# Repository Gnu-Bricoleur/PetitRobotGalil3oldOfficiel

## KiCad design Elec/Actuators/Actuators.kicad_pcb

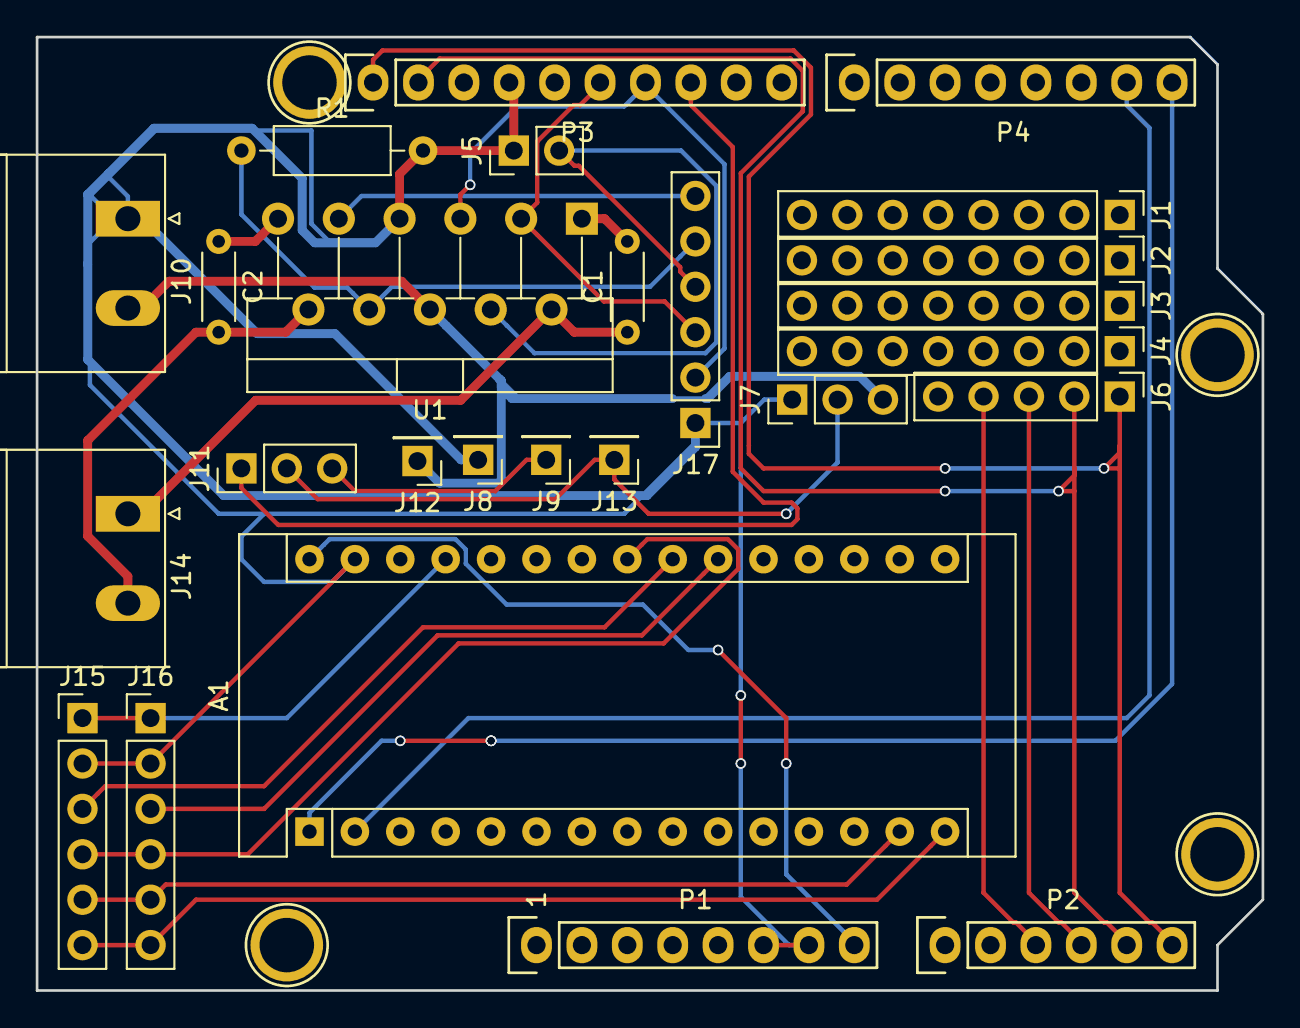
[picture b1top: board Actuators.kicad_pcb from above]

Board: 2 copper layers, 68.6 x 53.3 mm, 30 parts (0 on the bottom side), 27 nets.

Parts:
A1: Arduino_Nano_v3.x; Arduino_Nano
C1, C2: 10nF; R_Axial_DIN0204_L3.6mm_D1.6mm_P5.08mm_Horizontal
J1, J2, J3, J4: Conn_01x08; PinHeader_1x08_P2.54mm_Vertical
J5: Conn_01x02; PinHeader_1x02_P2.54mm_Vertical
J6: Conn_01x05; PinHeader_1x05_P2.54mm_Vertical
J7, J11: Conn_01x03; PinHeader_1x03_P2.54mm_Vertical
J8, J9, J12, J13: Conn_01x01; PinHeader_1x01_P2.54mm_Vertical
J10, J14: Screw_Terminal_01x02; PhoenixContact_MSTBA_2,5_2-G_1x02_P5.00mm_Horizontal
J15, J16, J17: Conn_01x06; PinHeader_1x06_P2.54mm_Vertical
P1: Power; Socket_Strip_Arduino_1x08
P2: Analog; Socket_Strip_Arduino_1x06
P3: Digital; Socket_Strip_Arduino_1x10
P4: Digital; Socket_Strip_Arduino_1x08
P5, P6, P7, P8: CONN_01X01; Arduino_1pin
R1: 2.7k; R_Axial_DIN0207_L6.3mm_D2.5mm_P10.16mm_Horizontal
U1: LMD18200; TO-220-11_P3.4x5.08mm_StaggerOdd_Lead4.85mm_Vertical

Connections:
/0(Rx): A1.1, P4.8
/1(Tx): A1.2, P4.7
/10(**/SS): J11.1, P3.8
/11(**/MOSI): J17.2, P3.7, U1.5
/12(MISO): J17.3, P3.6, U1.3
/A2: J6.4, P2.3
/A3: J6.3, P2.4
/A4(SDA): J6.2, P2.5, P3.2
/A5(SCL): J6.1, P2.6, P3.1
/BR1: J5.2, J17.4, U1.4
/Bat+: J7.3, J10.2, J12.1, U1.6
/CSEN1: J17.5, R1.1, U1.8
/EncAlim: A1.27, J15.1, J16.1
/MISO: A1.15, J15.6, J16.6
/MOSI: A1.14, J15.5, J16.5
/SCK: A1.23, J15.4, J16.4
/SS1: A1.22, J15.3
/SS2: A1.21, J16.3
/TF1: J17.6, U1.9
/Vin: A1.30, P1.8
GND: A1.29, J5.1, J7.1, J8.1, J10.1, J15.2, J16.2, J17.1, P1.6, P1.7, P3.4, R1.2, U1.7
unnamed: C1.1, J14.1, U1.2
unnamed: C1.2, U1.1
unnamed: C2.1, U1.11
unnamed: C2.2, J14.2, U1.10
unnamed: J7.2, J11.2, J13.1
unnamed: J9.1, J11.3

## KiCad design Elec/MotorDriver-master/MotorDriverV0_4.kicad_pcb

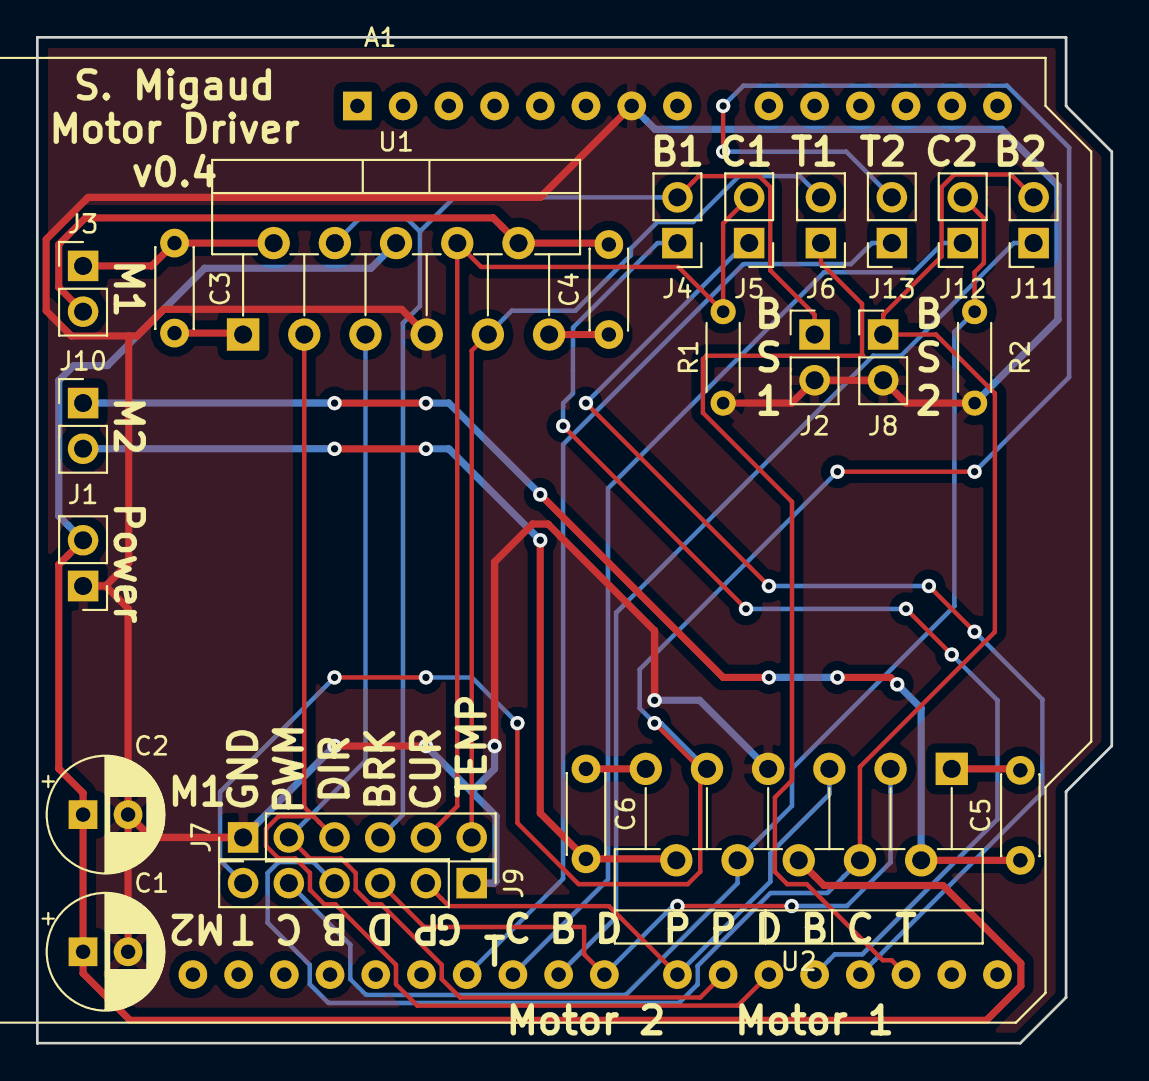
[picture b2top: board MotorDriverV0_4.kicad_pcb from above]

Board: 2 copper layers, 59.7 x 55.9 mm, 24 parts (0 on the bottom side), 26 nets.

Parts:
A1: Arduino_UNO_R3
C1: 1uF; CP_Radial_D6.3mm_P2.50mm
C2: 1200uF; CP_Radial_D6.3mm_P2.50mm
C3, C4, C5, C6: 10nF; C_Disc_D4.3mm_W1.9mm_P5.00mm
J1, J3, J10: Screw_Terminal_01x02; PinHeader_1x02_P2.54mm_Vertical
J2, J4, J5, J6, J8: Conn_01x02_Male; PinHeader_1x02_P2.54mm_Vertical
J7, J9: Conn_01x06_Male; PinHeader_1x06_P2.54mm_Vertical
J11, J12, J13: Conn_01x02_Male; PinSocket_1x02_P2.54mm_Vertical
R1, R2: 2.7k; R_Axial_DIN0204_L3.6mm_D1.6mm_P5.08mm_Horizontal
U1, U2: LMD18200; TO-220-11_P3.4x5.08mm_StaggerOdd_Lead4.85mm_Vertical

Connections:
BRK1: A1.19, J4.1
BRK2: A1.24, J11.1
CUR1: A1.18, J5.1
CUR2: A1.25, J12.1
DIR1: A1.20, J7.3, U1.3
DIR2: A1.23, J9.3, U2.3
GND: A1.7, C1.2, C2.2, J1.1, J2.2, J7.1, J8.2, J9.1, R1.1, R2.1, U1.7, U2.7
unnamed: C3.1, J3.1, U1.2
unnamed: C3.2, U1.1
unnamed: C4.1, U1.11
unnamed: C4.2, J3.2, U1.10
unnamed: C5.1, J10.1, U2.2
unnamed: C5.2, U2.1
unnamed: C6.1, U2.11
unnamed: C6.2, J10.2, U2.10
unnamed: J2.1, J4.2, J7.4, U1.4
unnamed: J5.2, J7.5, R1.2, U1.8
unnamed: J6.2, J7.6, U1.9
unnamed: J8.1, J9.4, J11.2, U2.4
unnamed: J9.5, J12.2, R2.2, U2.8
unnamed: J9.6, J13.2, U2.9
PWM1: A1.21, J7.2, U1.5
PWM2: A1.22, J9.2, U2.5
TEMP1: A1.17, J6.1
TEMP2: A1.26, J13.1
VS: C1.1, C2.1, J1.2, U1.6, U2.6

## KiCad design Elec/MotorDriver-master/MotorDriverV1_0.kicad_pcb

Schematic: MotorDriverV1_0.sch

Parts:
C1: 1uF; CP_Radial_D5.0mm_P2.50mm
C2: 0.33uF; R_Axial_DIN0204_L3.6mm_D1.6mm_P5.08mm_Horizontal
C3: 1200uF; CP_Radial_D7.5mm_P2.50mm
C4: 0.1uF; R_Axial_DIN0204_L3.6mm_D1.6mm_P5.08mm_Horizontal
C5, C6, C7, C8: 10nF; R_Axial_DIN0204_L3.6mm_D1.6mm_P5.08mm_Horizontal
D1, D2, D3, D4: LED; LED_0603_1608Metric_Pad1.05x0.95mm_HandSolder
D5: LED; PinHeader_1x02_P2.54mm_Vertical
J1, J5, J6: Screw_Terminal_01x02; PhoenixContact_MSTBA_2,5_2-G_1x02_P5.00mm_Horizontal
J2, J3, J4: Conn_01x02; PinHeader_1x02_P2.54mm_Vertical
J7, J8, J9, J11, J12, J13: Conn_01x01; PinHeader_1x01_P2.54mm_Vertical
J10: Conn_02x06_Odd_Even; IDC-Header_2x06_P2.54mm_Vertical
P1: Power; Socket_Strip_Arduino_1x08
P2: Analog; Socket_Strip_Arduino_1x06
P3: Digital; Socket_Strip_Arduino_1x10
P4: Digital; Socket_Strip_Arduino_1x08
P5, P6, P7, P8: CONN_01X01; Arduino_1pin
R1, R3, R4: 1k; R_0603_1608Metric_Pad1.05x0.95mm_HandSolder
R2: 1K; R_0603_1608Metric_Pad1.05x0.95mm_HandSolder
R5, R6: 2.7k; R_Axial_DIN0207_L6.3mm_D2.5mm_P10.16mm_Horizontal
R7: 1k; R_Axial_DIN0207_L6.3mm_D2.5mm_P10.16mm_Horizontal
U1: LM324; SOIC-14_3.9x8.7mm_P1.27mm
U2: L7809; PinHeader_1x03_P2.54mm_Vertical
U3, U4: LMD18200; TO-220-11_P3.4x5.08mm_StaggerOdd_Lead4.85mm_Vertical

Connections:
+5V: P1.5, U1.4 (V+)
/2: J10.7, P4.6, U1.5 (+), U3.3
/3(**): J10.9, P4.5, U1.3 (+), U3.5
/4: J10.6, P4.4, U1.12 (+), U4.3
/5(**): J10.4, P4.3, U1.10 (+), U4.5
/6(**): J9.1, P4.2
/7: J7.1, P4.1
/8: J11.1, P3.10
/9(**): J13.1, P3.9
/A0: J8.1, P2.1
/A1: J12.1, P2.2
/BR1: J3.2, J10.5, U3.4
/BR2: J4.2, J10.8, U4.4
/CSEN1: J10.3, R5.1, U3.8
/CSEN2: J10.10, R6.1, U4.8
/TF1: J10.1, U3.9
/TF2: J10.12, U4.9
/Vin: C4.1, D5.2, P1.8, U2.3 (OUT)
/Vs: C1.1, C3.1, J1.2, J2.1, U3.6, U4.6
GND: C1.2, C2.2, C3.2, C4.2, J1.1, J3.1, J4.1, J10.2, J10.11, P1.6, P1.7, P3.4, R1.1, R2.1, R3.1, R4.1, R5.2, R6.2, R7.2, U1.11 (V-), U2.2 (GND), U3.7, U4.7
unnamed: C2.1, J2.2, U2.1 (IN)
unnamed: C5.1, J5.1, U3.2
unnamed: C5.2, U3.1
unnamed: C6.1, U3.11
unnamed: C6.2, J5.2, U3.10
unnamed: C7.1, J6.1, U4.2
unnamed: C7.2, U4.1
unnamed: C8.1, U4.11
unnamed: C8.2, J6.2, U4.10
unnamed: D1.1, R1.2
unnamed: D1.2, U1.1, U1.2 (-)
unnamed: D2.1, R2.2
unnamed: D2.2, U1.6 (-), U1.7
unnamed: D3.1, R3.2
unnamed: D3.2, U1.8, U1.9 (-)
unnamed: D4.1, R4.2
unnamed: D4.2, U1.13 (-), U1.14
unnamed: D5.1, R7.1

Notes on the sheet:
Holes
Shield for Arduino that uses the same pin disposition like "Uno" board Rev 3.
BR1 -- 6(**) CSEN1 -- A0 TF1 -- 7 BR2 -- 8 CSEN2 -- A1 TF2 -- 9(**) positionne de facon a mettre un jumper en configuration shield

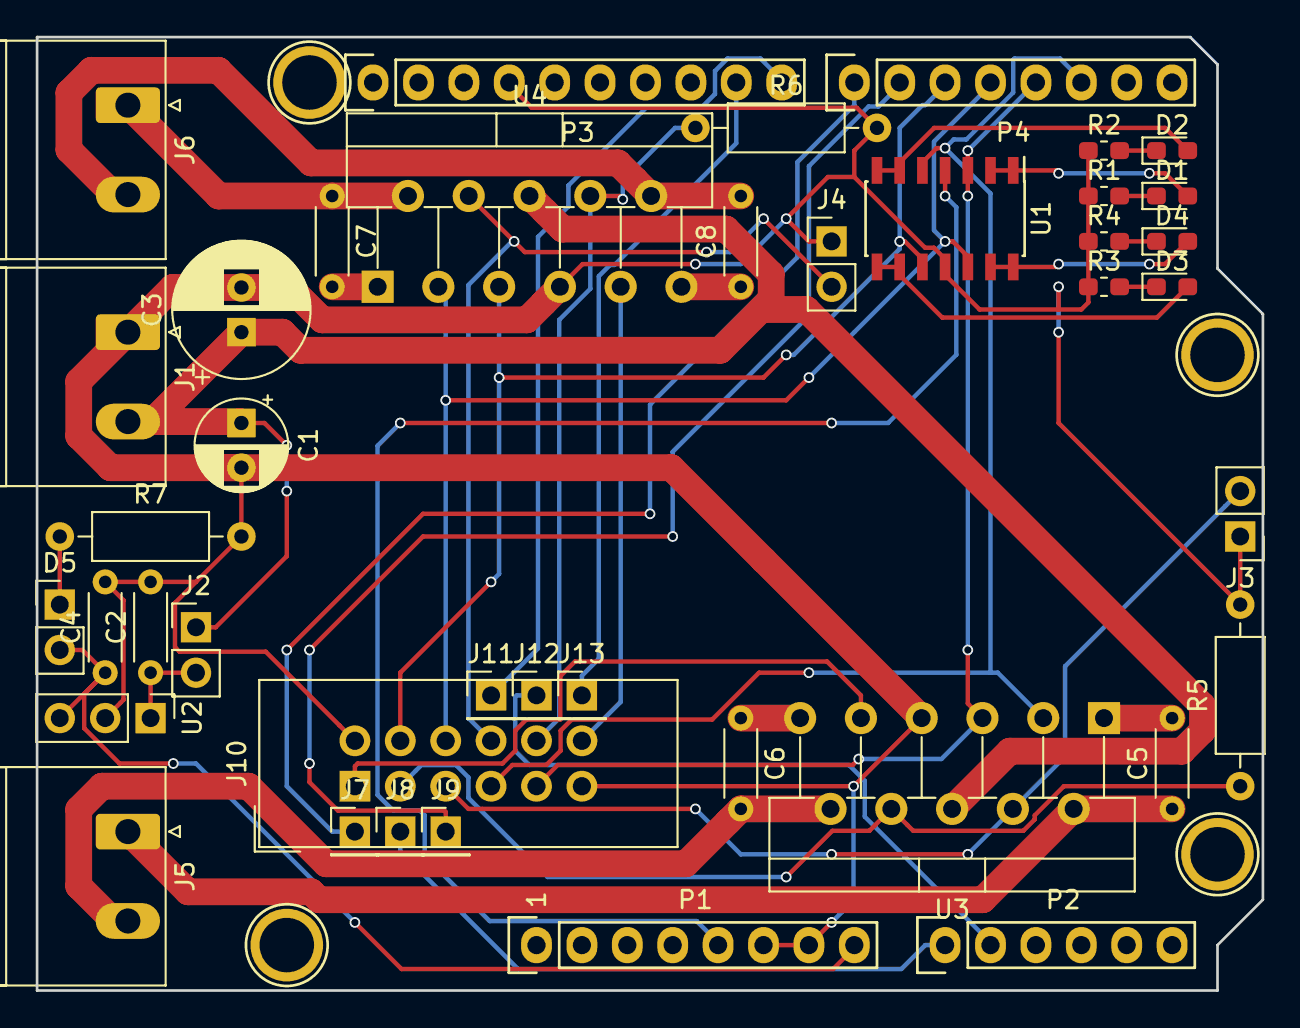
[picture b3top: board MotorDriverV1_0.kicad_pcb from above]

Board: 2 copper layers, 68.6 x 53.3 mm, 45 parts (0 on the bottom side), 38 nets.

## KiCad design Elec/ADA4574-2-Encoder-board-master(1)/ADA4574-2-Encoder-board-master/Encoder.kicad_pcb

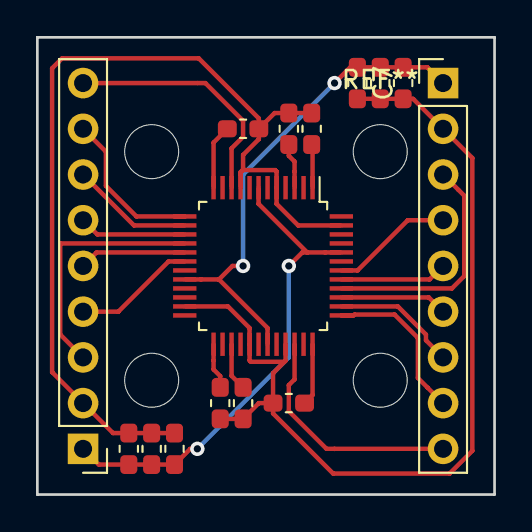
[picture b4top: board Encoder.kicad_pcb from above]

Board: 2 copper layers, 25.4 x 25.4 mm, 15 parts (0 on the bottom side), 24 nets.

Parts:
C1, C12: 4.7uF; C_0603_1608Metric_Pad1.05x0.95mm_HandSolder
C2, C3, C10, C11: 100nF; C_0603_1608Metric_Pad1.05x0.95mm_HandSolder
C4, C9: 220nF; C_0603_1608Metric_Pad1.05x0.95mm_HandSolder
C5, C6, C7, C8: 1uF; C_0603_1608Metric_Pad1.05x0.95mm_HandSolder
J1, J2: Conn_01x09; PinHeader_1x09_P2.54mm_Vertical
U1: ADA4574-2; LQFP-48_7x7mm_P0.5mm

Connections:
+5V: C1.1, C5.1, C6.1, J1.1, U1.7, U1.44
+5VA: C7.1, C8.1, C12.1, J2.1, U1.20, U1.31
GND: C1.2, C2.1, C3.2, C4.1, C5.2, C6.2, J1.2, U1.5, U1.9, U1.47
GNDA: C7.2, C8.2, C9.2, C10.1, C11.2, C12.2, J2.2, U1.23, U1.29, U1.33
unnamed: C2.2, U1.1
unnamed: C3.1, U1.3
unnamed: C4.2, U1.12
unnamed: C9.1, U1.36
unnamed: C10.2, U1.27
unnamed: C11.1, U1.25
unnamed: J1.3, U1.16
unnamed: J1.4, U1.18
unnamed: J1.5, U1.17
unnamed: J1.6, U1.15
unnamed: J1.7, U1.14
unnamed: J1.8, U1.13
unnamed: J1.9, U1.10
unnamed: J2.3, U1.40
unnamed: J2.4, U1.42
unnamed: J2.5, U1.41
unnamed: J2.6, U1.39
unnamed: J2.7, U1.38
unnamed: J2.8, U1.37
unnamed: J2.9, U1.34

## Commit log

2019-01-30 3D start tracking
2019-02-08 bottom and sides
2019-02-18 front and back before interlock
2019-02-18 before LCI
2019-02-18 before screw
2019-02-19 svg for trotec
2019-03-20 blabla
2019-04-03 3d a jour
2019-04-04 compiled everything together
2019-04-27 Main Nucleo
2019-05-01 V4 need assembly
2019-05-02 V4 assembled
2019-05-04 newWheel
2019-05-07 Position working git add *git add *
2019-05-09 actuators
2019-05-09 lci svg
2019-05-09 PID en cours
2019-05-22 need big cleanup
2019-05-23 slightly cleaned, needs tests
2019-05-26 fin de we
2019-05-27 nano detection
2019-05-27 CA ROULE DROOOOOOOIIIIIIITTTTT fine tuning of the pid to be done
2019-05-27 ca tourne
2019-05-28 miscanelous functions
2019-05-28 tourne mieux mais necsessite meilleure gestion distance
2019-05-28 some improvements on the code but weirdly doesn't build anymore....
2019-05-28 solve makefile issue
2019-05-30 code homo
2019-05-30 premier match
2019-05-30 asser corrige marche arriere et relatif
2019-05-30 trajec bonnes, moteur HS ?
2019-05-31 trajectoires ameillore avant 4eme match
2019-06-02 fin de coupe
